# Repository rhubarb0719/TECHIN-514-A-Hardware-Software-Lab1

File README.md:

# TECHIN514_W26

yilu's homeworks

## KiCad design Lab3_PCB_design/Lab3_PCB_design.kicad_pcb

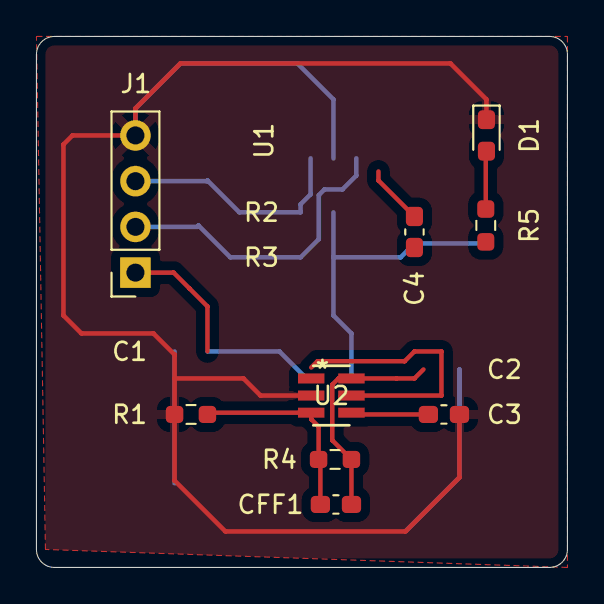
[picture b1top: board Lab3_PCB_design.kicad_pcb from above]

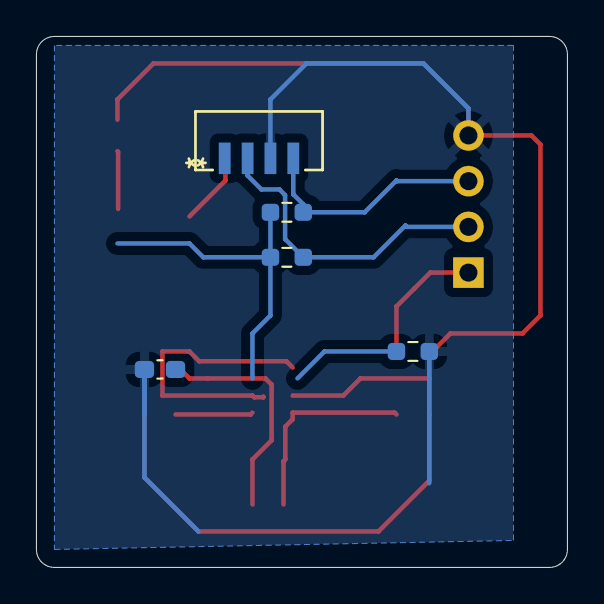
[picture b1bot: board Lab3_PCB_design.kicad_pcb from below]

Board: 2 copper layers, 29.5 x 29.5 mm, 14 parts (5 on the bottom side), 11 nets.

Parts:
C1: 1µF; R_0603_1608Metric_Pad0.98x0.95mm_HandSolder
C2: 2.2µF; C_0603_1608Metric_Pad1.08x0.95mm_HandSolder
C3: 0.01µF; C_0603_1608Metric_Pad1.08x0.95mm_HandSolder
C4: 0.1µF; C_0603_1608Metric_Pad1.08x0.95mm_HandSolder
CFF1: 15pF; C_0603_1608Metric_Pad1.08x0.95mm_HandSolder
D1: LED; LED_0603_1608Metric_Pad1.05x0.95mm_HandSolder
J1: Conn_01x04_Pin; PinSocket_1x04_P2.54mm_Vertical
R1: 30.1kΩ; R_0603_1608Metric_Pad0.98x0.95mm_HandSolder
R2, R3: 4.7 kΩ; R_0603_1608Metric_Pad0.98x0.95mm_HandSolder
R4: 51kΩ; R_0603_1608Metric_Pad0.98x0.95mm_HandSolder
R5: 2.2kΩ; R_0603_1608Metric_Pad0.98x0.95mm_HandSolder
U1: VEML7700-TT; SMT_L7700-TT_VIS
U2: TPS79301DBVR; DBV6

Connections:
+3.3V: R2.1, R3.1
+3V3: C4.2, R5.1
GND: C1.2, C2.1, C3.2, D1.1 (K), J1.4 (GND), R1.1, U1.3 (GND), U2.2 (GND)
unnamed: D1.2 (A), R5.2
unnamed: J1.3 (SCL), R2.2, U1.4 (SDA)
unnamed: J1.2 (SDA), R3.2, U1.2 (VDD)
unnamed: C4.1, U1.1 (SCL)
unnamed: CFF1.1, R1.2, R4.1, U2.3 (FB)
unnamed: C3.1, U2.4 (NR)
Vin: C1.1, U2.1 (IN), U2.5 (EN)
Vout: C2.2, CFF1.2, R4.2, U2.6 (OUT)

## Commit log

2026-01-08 Add initial README with course information
2026-01-08 Add Lab1 PlatformIO project files
2026-01-14 Create lab2
2026-01-30 lab3
